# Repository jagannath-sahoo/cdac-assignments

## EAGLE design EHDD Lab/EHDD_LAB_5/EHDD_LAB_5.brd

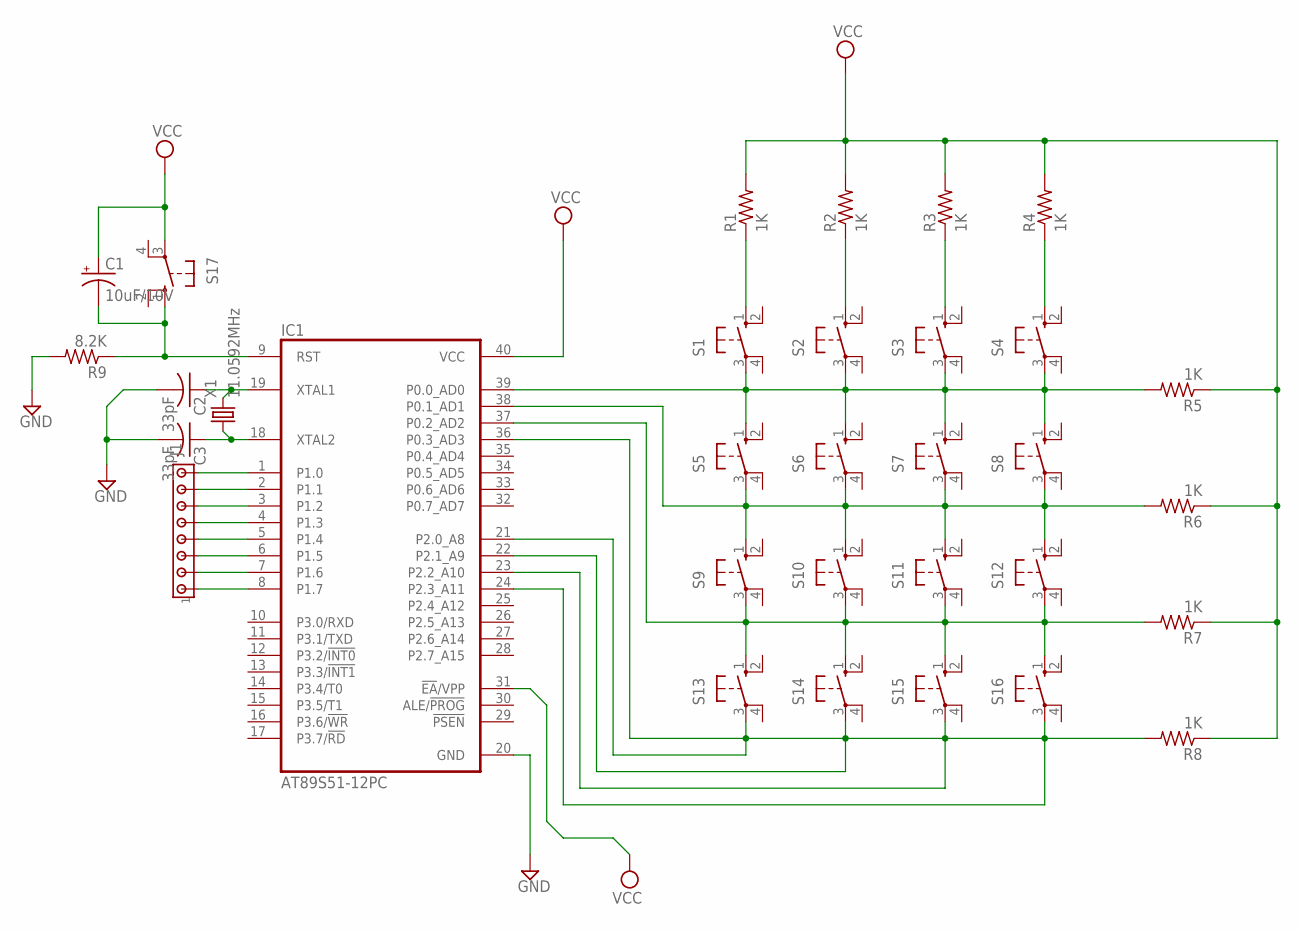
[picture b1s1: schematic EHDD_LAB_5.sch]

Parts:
C1: 10uF/10V; 153CLV-0505
C2, C3: 33pF; C0603
IC1: AT89S51-12PC; DIL40
J1: MTA08-100; 10X08MTA
R1, R2, R3, R4, R5, R6, R7, R8: 1K; R0603
R9: 8.2K; R0603
S1, S2, S3, S4, S5, S6, S7, S8, S9, S10, S11, S12, S13, S14, S15, S16, S17: 10-XX; B3F-10XX
X1: 11.0592MHz; HC49

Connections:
GND: C2.2, C3.2, IC1.20 (GND), R9.2
unnamed: R1.1, S1.1 (S)
unnamed: R2.1, S2.1 (S)
unnamed: R3.1, S3.1 (S)
unnamed: R4.1, S4.1 (S)
unnamed: IC1.39 (P0.0_AD0), R5.2, S1.3, S2.3, S3.3, S4.3, S5.1 (S), S6.1 (S), S7.1 (S), S8.1 (S)
unnamed: IC1.1 (P1.0), J1.8
unnamed: IC1.2 (P1.1), J1.7
unnamed: IC1.38 (P0.1_AD1), R6.2, S5.3, S6.3, S7.3, S8.3, S9.1 (S), S10.1 (S), S11.1 (S), S12.1 (S)
unnamed: IC1.3 (P1.2), J1.6
unnamed: IC1.4 (P1.3), J1.5
unnamed: IC1.5 (P1.4), J1.4
unnamed: IC1.37 (P0.2_AD2), R7.2, S9.3, S10.3, S11.3, S12.3, S13.1 (S), S14.1 (S), S15.1 (S), S16.1 (S)
unnamed: IC1.6 (P1.5), J1.3
unnamed: IC1.7 (P1.6), J1.2
unnamed: IC1.8 (P1.7), J1.1
unnamed: IC1.21 (P2.0_A8), IC1.22 (P2.1_A9), IC1.23 (P2.2_A10), IC1.24 (P2.3_A11), IC1.36 (P0.3_AD3), R8.2, S13.3, S14.3, S15.3, S16.3
unnamed: C1.-, IC1.9 (RST), R9.1, S17.1 (S)
unnamed: C2.1, IC1.19 (XTAL1), X1.2
unnamed: C3.1, IC1.18 (XTAL2), X1.1
VCC: C1.+, IC1.31 (!EA!/VPP), IC1.40 (VCC), R1.2, R2.2, R3.2, R4.2, R5.1, R6.1, R7.1, R8.1, S17.3

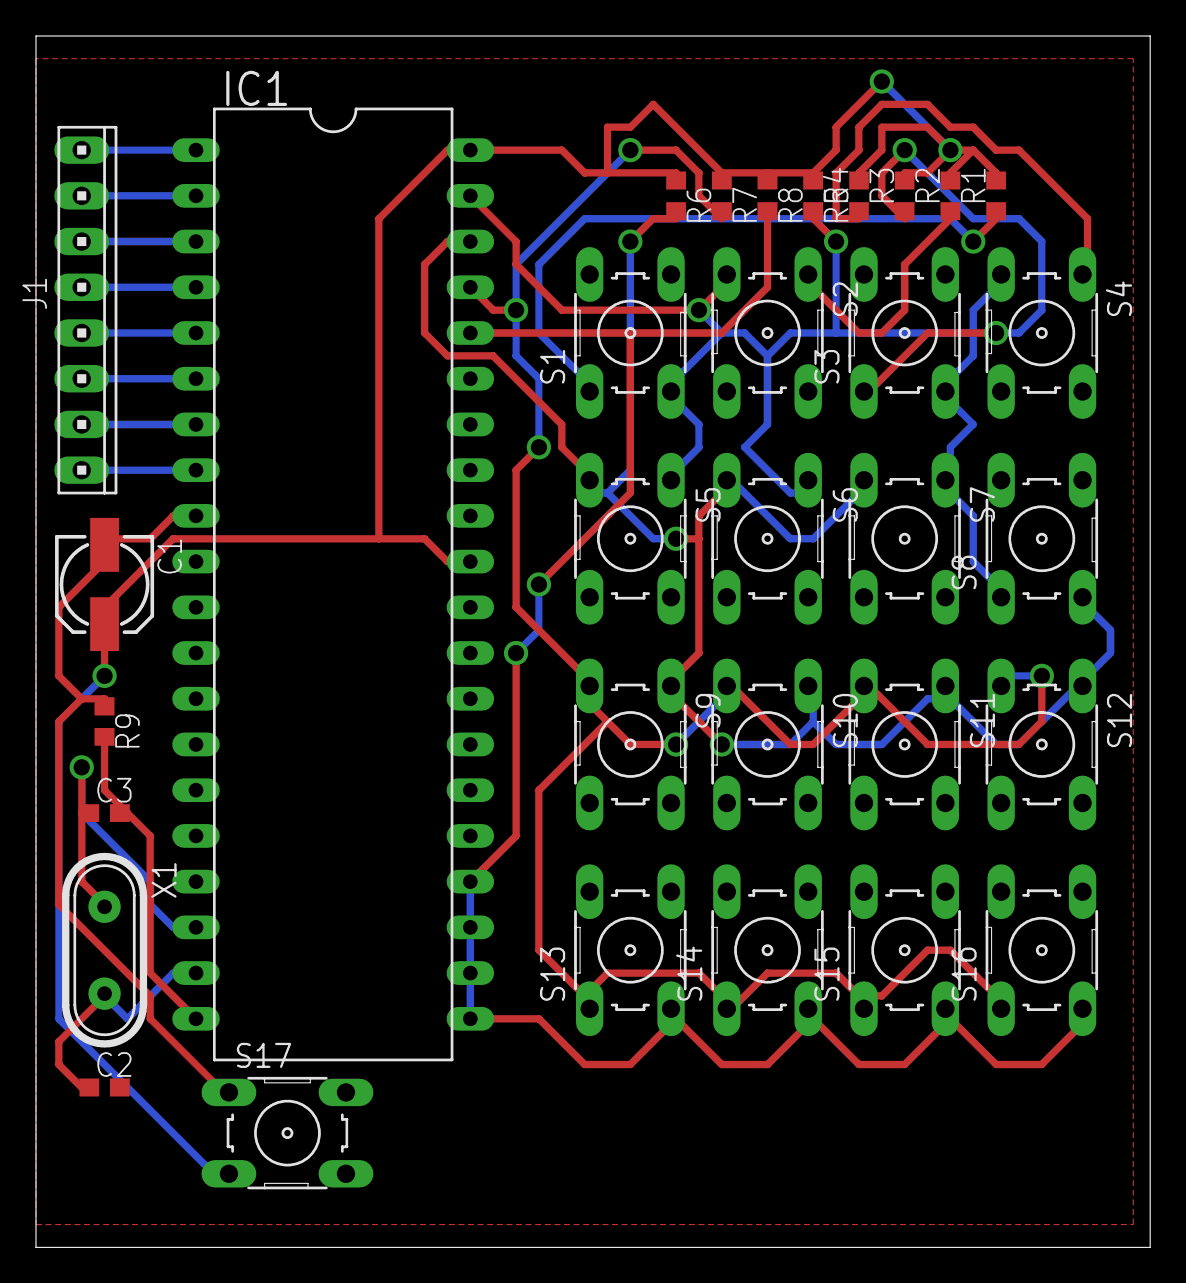
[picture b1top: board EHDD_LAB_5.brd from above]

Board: 2 copper layers, 61.9 x 67.3 mm, 32 parts (0 on the bottom side), 21 nets.

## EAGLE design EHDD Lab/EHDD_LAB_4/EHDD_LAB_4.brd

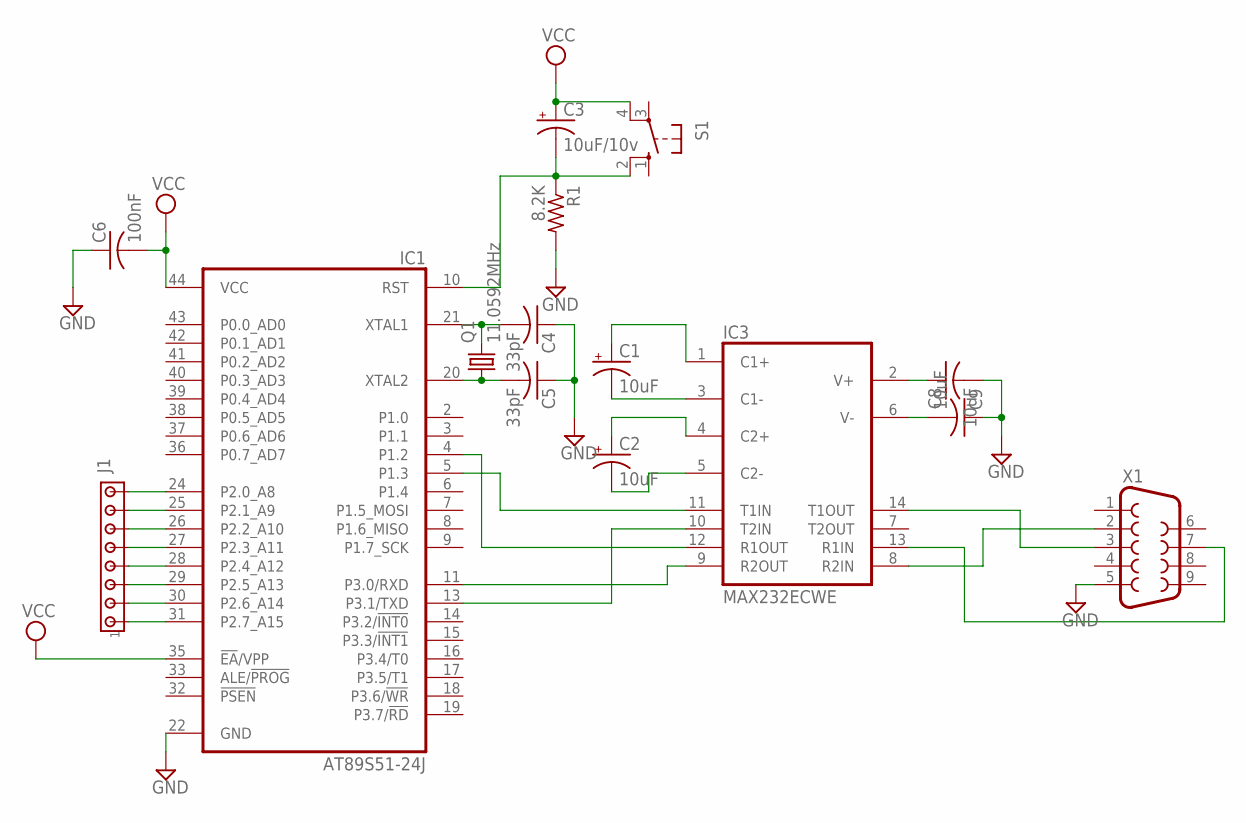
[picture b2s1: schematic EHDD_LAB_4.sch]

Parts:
C1, C2: 10uF; 153CLV-0405
C3: 10uF/10v; 153CLV-0405
C4, C5: 33pF; C0805
C6: 100nF; C0805
C8, C9: 10uF; C0805
IC1: AT89S51-24J; PLCC44
IC3: MAX232ECWE; SO16L
J1: MTA08-100; 10X08MTA
Q1: 11.0592MHz; TC38H
R1: 8.2K; R0805
S1: 10-XX; B3F-10XX
X1: F09V

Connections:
GND: C4.1, C5.1, C6.1, C8.2, C9.1, IC1.22 (GND), IC3.15 (GND), R1.2, X1.5
unnamed: IC1.5 (P1.3), IC3.11 (T1IN)
unnamed: IC1.13 (P3.1/TXD), IC3.10 (T2IN)
unnamed: IC1.4 (P1.2), IC3.12 (R1OUT)
unnamed: IC1.11 (P3.0/RXD), IC3.9 (R2OUT)
unnamed: C2.-, IC3.5 (C2-)
unnamed: C2.+, IC3.4 (C2+)
unnamed: C1.-, IC3.3 (C1-)
unnamed: C1.+, IC3.1 (C1+)
unnamed: C9.2, IC3.6 (V-)
unnamed: C8.1, IC3.2 (V+)
unnamed: IC3.14 (T1OUT), X1.3
unnamed: IC3.8 (R2IN), X1.2
unnamed: IC3.13 (R1IN), X1.7
unnamed: IC1.24 (P2.0_A8), J1.8
unnamed: IC1.25 (P2.1_A9), J1.7
unnamed: IC1.26 (P2.2_A10), J1.6
unnamed: IC1.27 (P2.3_A11), J1.5
unnamed: IC1.28 (P2.4_A12), J1.4
unnamed: IC1.29 (P2.5_A13), J1.3
unnamed: IC1.30 (P2.6_A14), J1.2
unnamed: IC1.31 (P2.7_A15), J1.1
unnamed: C5.2, IC1.20 (XTAL2), Q1.1
unnamed: C4.2, IC1.21 (XTAL1), Q1.2
unnamed: C3.-, IC1.10 (RST), R1.1, S1.2 (S1)
VCC: C3.+, C6.2, IC1.35 (!EA!/VPP), IC1.44 (VCC), IC3.16 (VCC), S1.4 (P1)

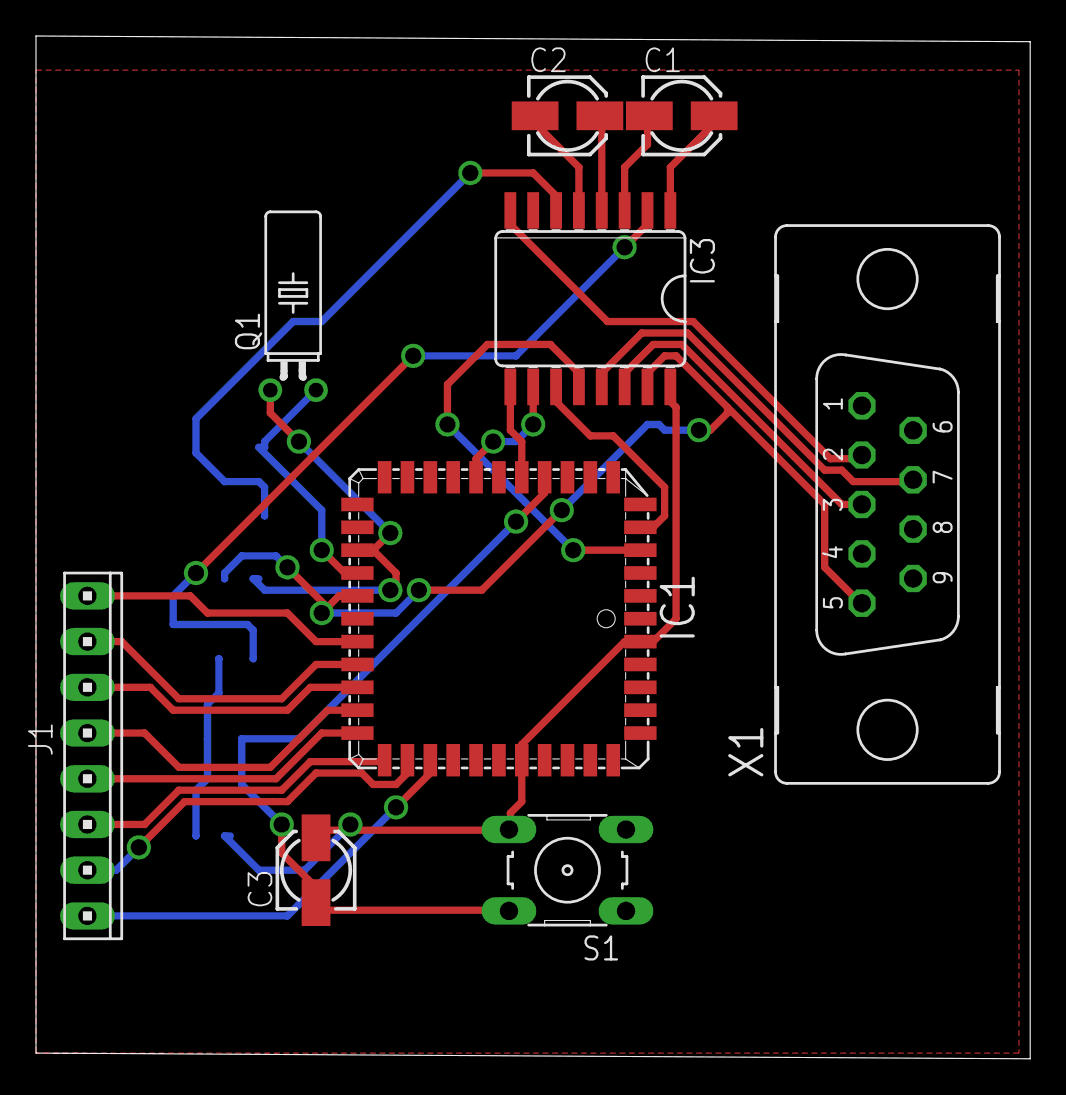
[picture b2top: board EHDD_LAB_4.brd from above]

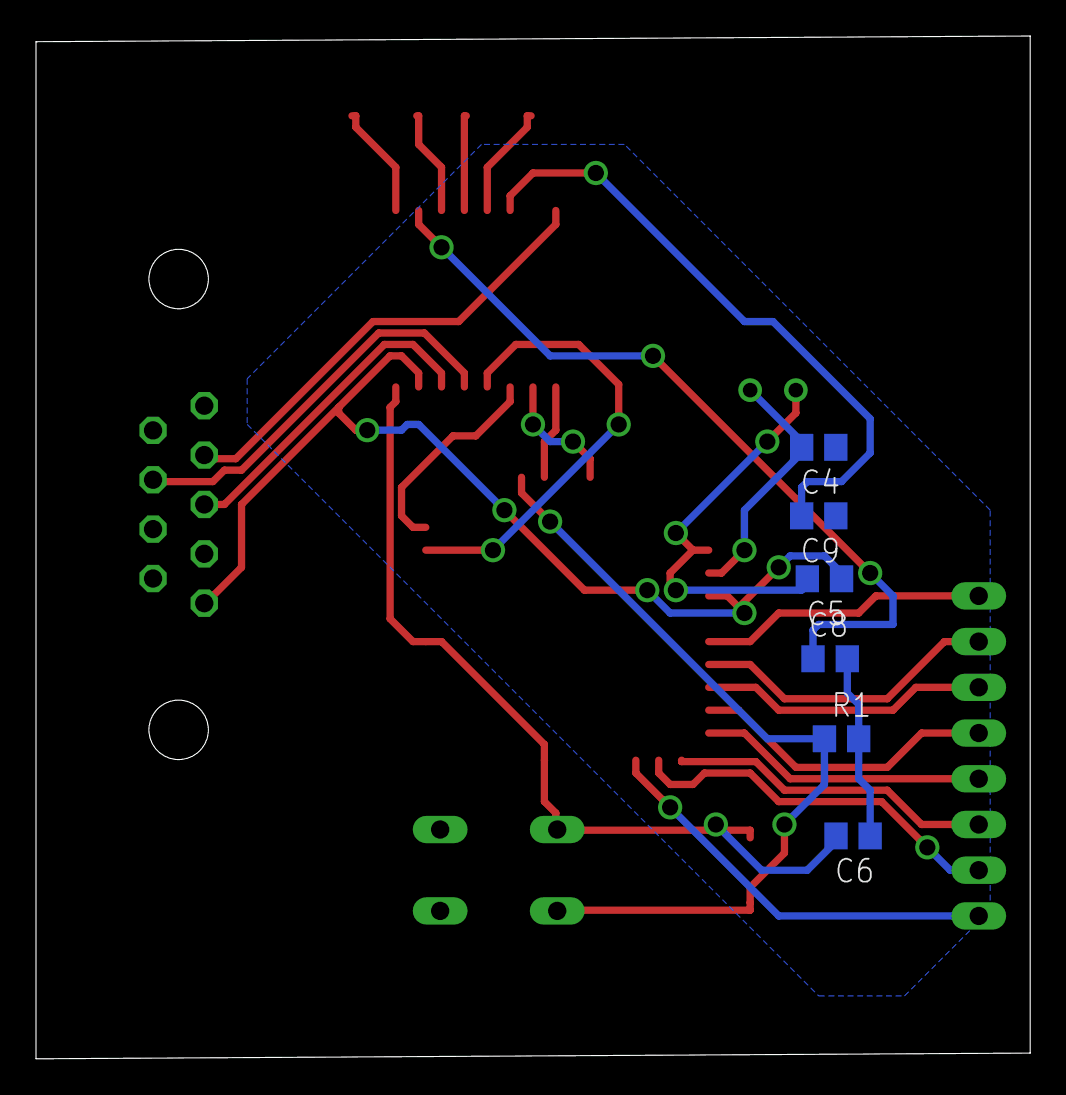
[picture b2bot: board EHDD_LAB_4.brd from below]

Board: 2 copper layers, 55.2 x 56.8 mm, 15 parts (6 on the bottom side), 26 nets.

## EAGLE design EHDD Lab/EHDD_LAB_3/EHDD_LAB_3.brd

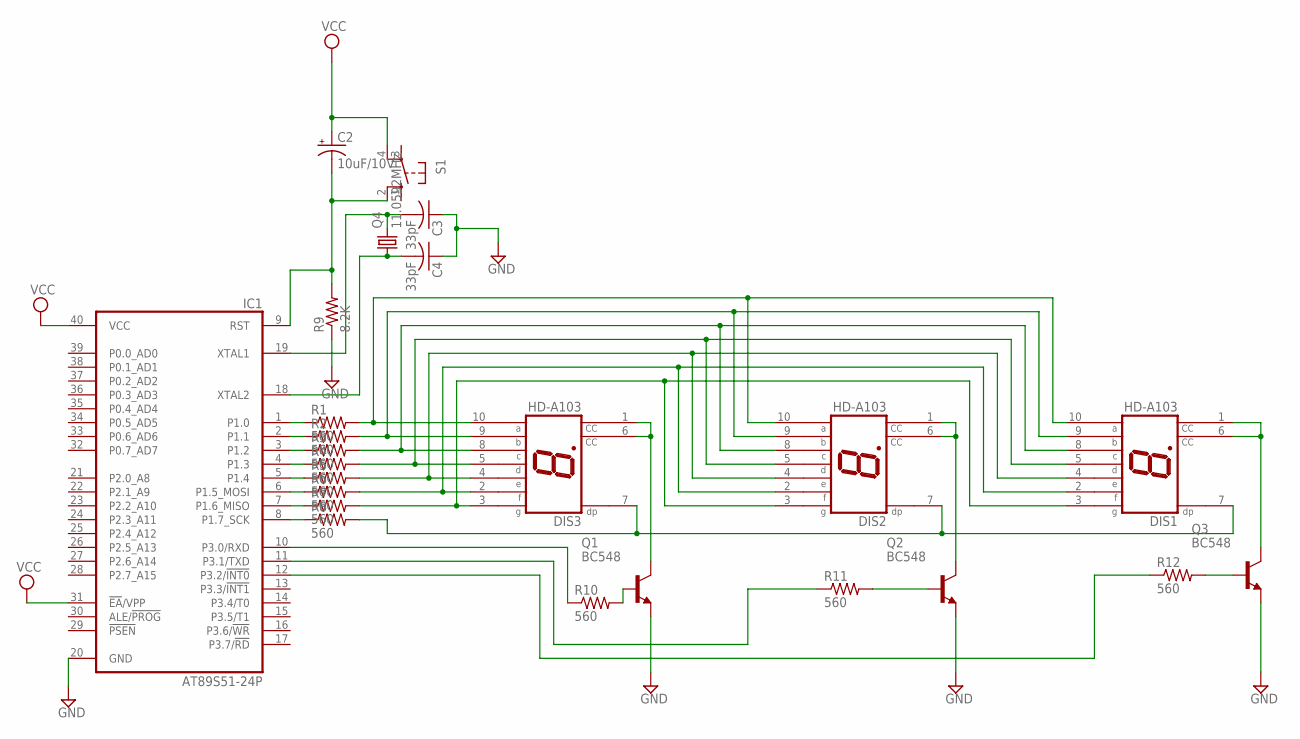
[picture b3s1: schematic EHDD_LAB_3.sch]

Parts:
C2: 10uF/10V; E2-5
C3, C4: 33pF; C025-050X050
DIS1, DIS2, DIS3: HD-A103; HDSP-A
IC1: AT89S51-24P; DIL40
Q1, Q2, Q3: BC548; TO92-EBC
Q4: 11.0592MHz; TC38H
R1, R2, R3, R4, R5, R6, R7, R8, R10, R11, R12: 560; 0207/10
R9: 8.2K; 0207/10
S1: 10-XX; B3F-10XX

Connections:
GND: C3.1, C4.1, IC1.20 (GND), Q1.E, Q2.E, Q3.E, R9.1
unnamed: DIS1.8 (C), DIS2.8 (C), DIS3.8 (C), R3.2
unnamed: DIS1.9 (B), DIS2.9 (B), DIS3.9 (B), R2.2
unnamed: DIS3.1 (CC), DIS3.6 (CC), Q1.C
unnamed: DIS1.5 (D), DIS2.5 (D), DIS3.5 (D), R4.2
unnamed: DIS1.4 (E), DIS2.4 (E), DIS3.4 (E), R5.2
unnamed: DIS1.2 (F), DIS2.2 (F), DIS3.2 (F), R6.2
unnamed: DIS1.3 (G), DIS2.3 (G), DIS3.3 (G), R7.2
unnamed: DIS1.7 (DP), DIS2.7 (DP), DIS3.7 (DP), R8.2
unnamed: IC1.1 (P1.0), R1.1
unnamed: IC1.2 (P1.1), R2.1
unnamed: IC1.3 (P1.2), R3.1
unnamed: IC1.4 (P1.3), R4.1
unnamed: IC1.5 (P1.4), R5.1
unnamed: IC1.6 (P1.5_MOSI), R6.1
unnamed: IC1.7 (P1.6_MISO), R7.1
unnamed: IC1.8 (P1.7_SCK), R8.1
unnamed: DIS1.10 (A), DIS2.10 (A), DIS3.10 (A), R1.2
unnamed: DIS2.1 (CC), DIS2.6 (CC), Q2.C
unnamed: DIS1.1 (CC), DIS1.6 (CC), Q3.C
unnamed: IC1.10 (P3.0/RXD), R10.1
unnamed: IC1.11 (P3.1/TXD), R11.1
unnamed: IC1.12 (P3.2/!INT0), R12.1
unnamed: C2.-, IC1.9 (RST), R9.2, S1.2 (S1)
unnamed: Q1.B, R10.2
unnamed: C3.2, IC1.19 (XTAL1), Q4.2
unnamed: C4.2, IC1.18 (XTAL2), Q4.1
unnamed: Q2.B, R11.2
unnamed: Q3.B, R12.2
VCC: C2.+, IC1.31 (!EA!/VPP), IC1.40 (VCC), S1.4 (P1)

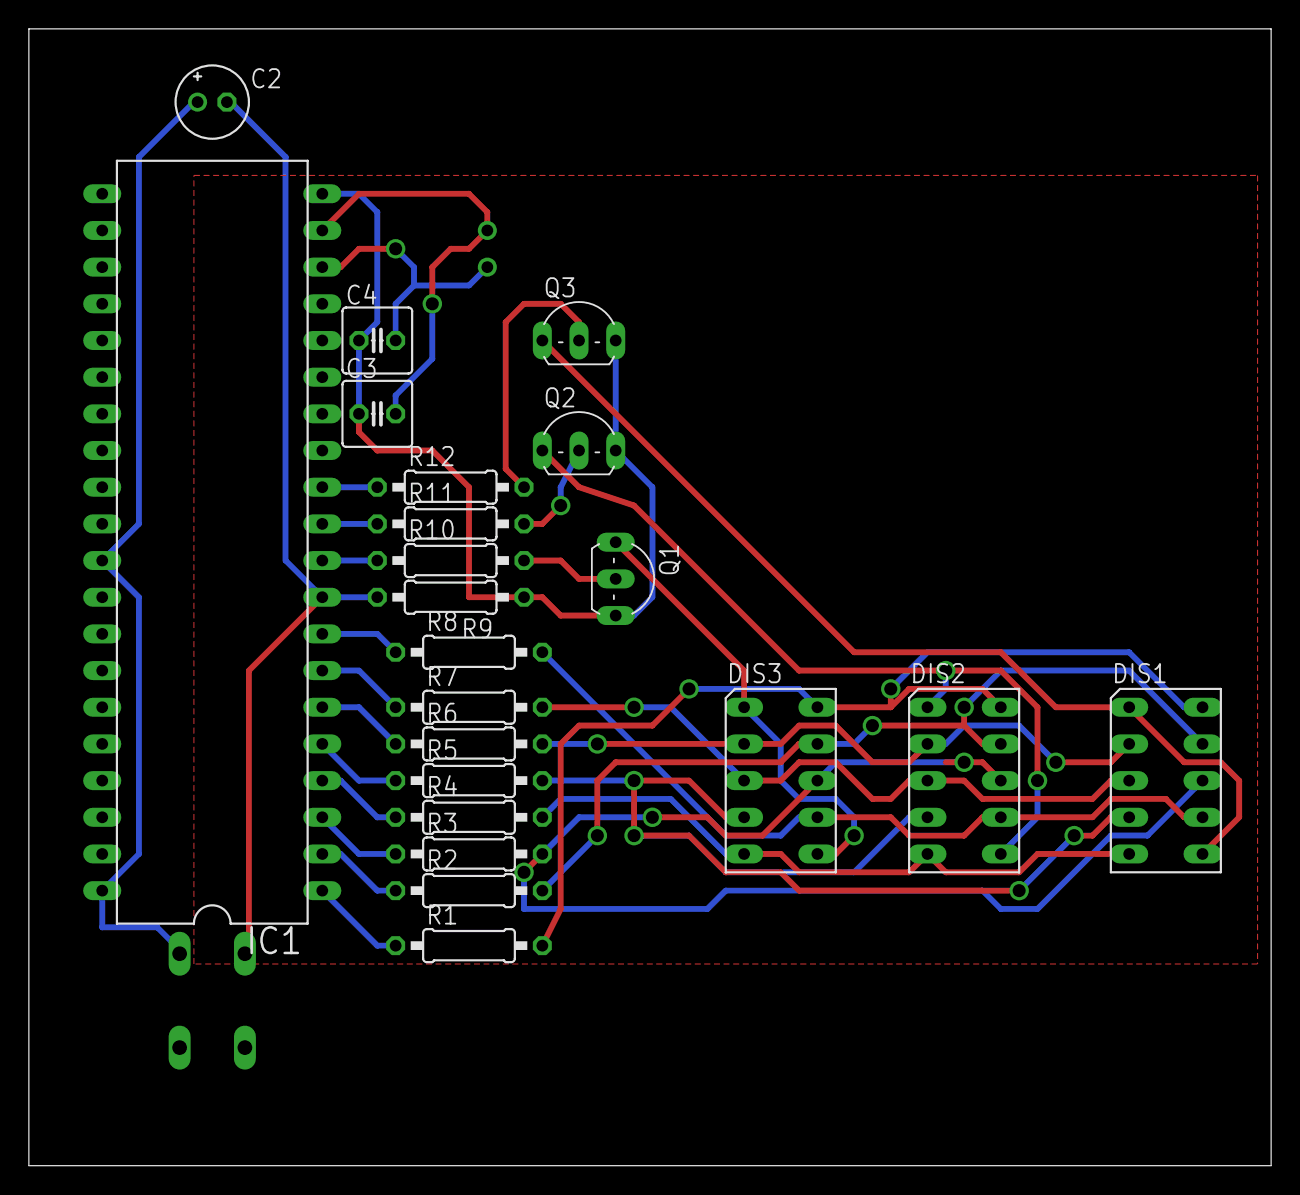
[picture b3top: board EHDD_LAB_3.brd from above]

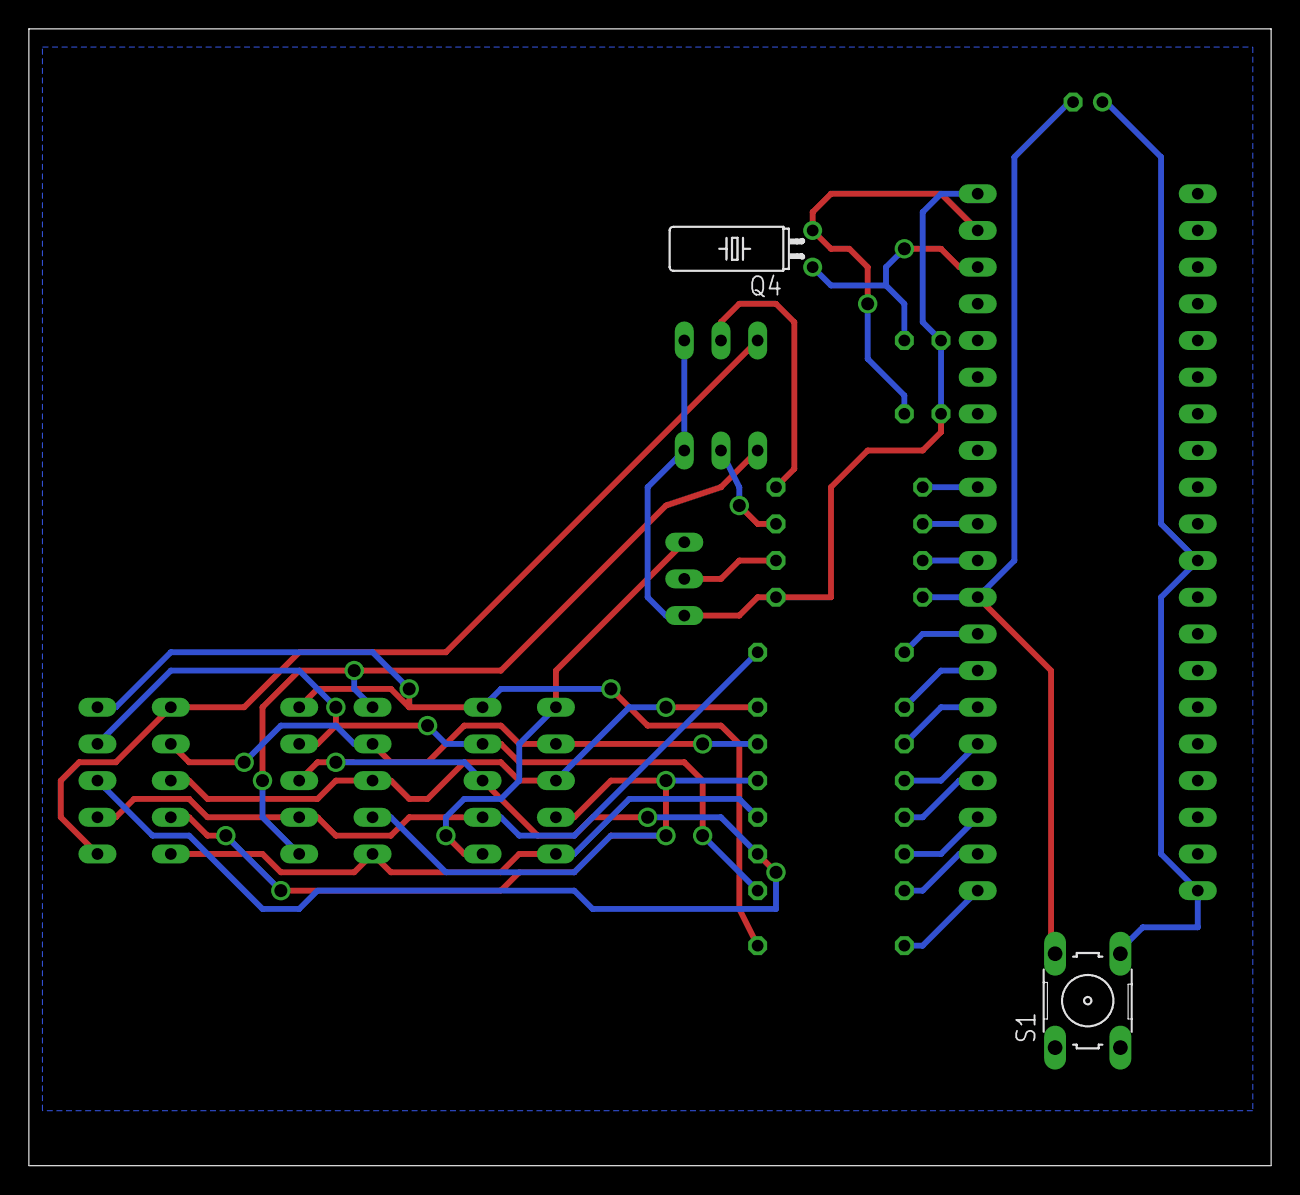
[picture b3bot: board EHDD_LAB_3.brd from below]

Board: 2 copper layers, 86.0 x 78.7 mm, 24 parts (2 on the bottom side), 30 nets.

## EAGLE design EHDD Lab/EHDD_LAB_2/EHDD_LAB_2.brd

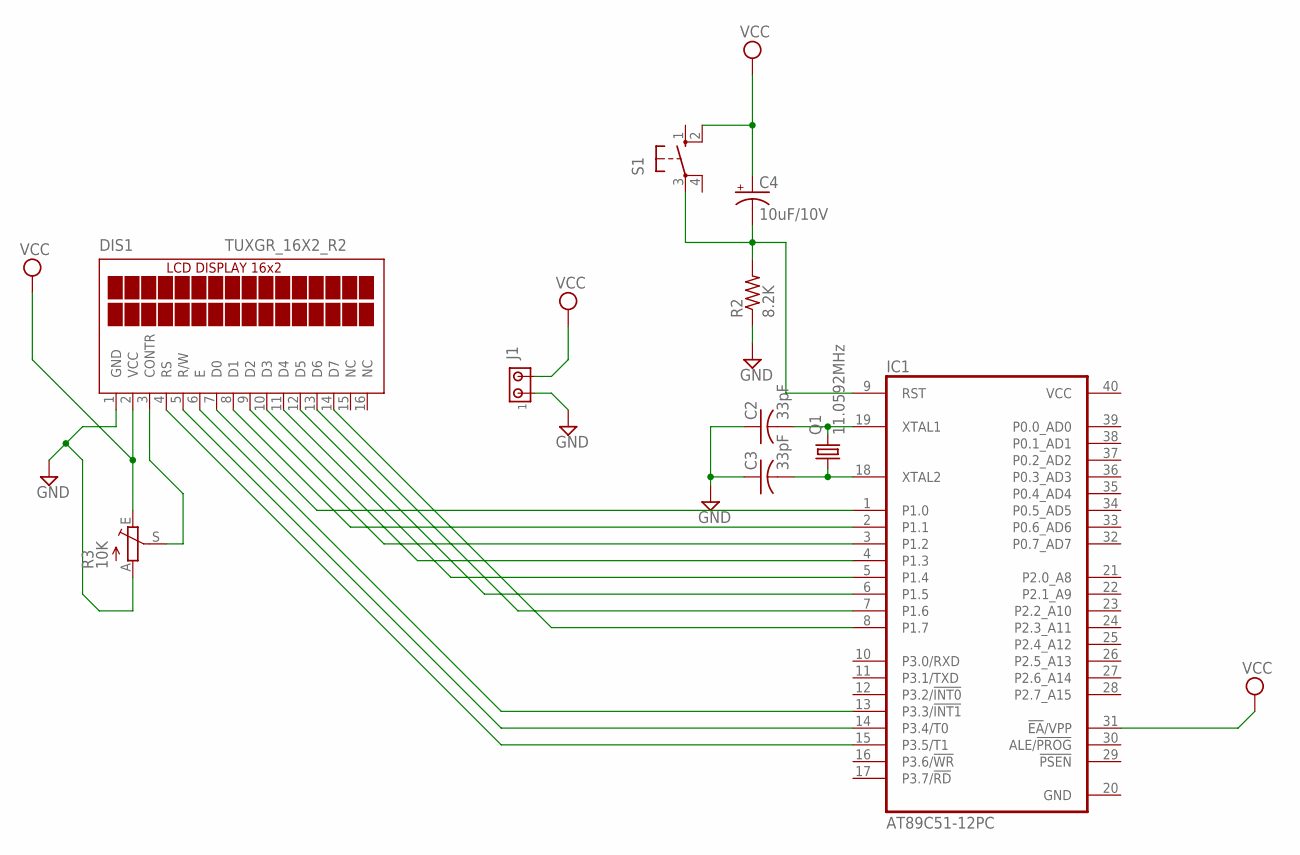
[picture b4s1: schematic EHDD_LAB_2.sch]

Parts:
C2, C3: 33pF; C025-025X050
C4: 10uF/10V; E2,5-5
DIS1: TUXGR_16X2_R2
IC1: AT89C51-12PC; DIL40
J1: MTA02-100; 10X02MTA
Q1: 11.0592MHz; TC26H
R2: 8.2K; R2512
R3: 10K; B25U
S1: 10-XX; B3F-10XX

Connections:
GND: C2.1, C3.1, DIS1.1 (GND), IC1.20 (GND), J1.1, R2.1, R3.A
unnamed: C4.-, IC1.9 (RST), R2.2, S1.3
unnamed: C2.2, IC1.19 (XTAL1), Q1.2
unnamed: C3.2, IC1.18 (XTAL2), Q1.1
unnamed: DIS1.7 (D0), IC1.1 (P1.0)
unnamed: DIS1.8 (D1), IC1.2 (P1.1)
unnamed: DIS1.9 (D2), IC1.3 (P1.2)
unnamed: DIS1.10 (D3), IC1.4 (P1.3)
unnamed: DIS1.11 (D4), IC1.5 (P1.4)
unnamed: DIS1.12 (D5), IC1.6 (P1.5)
unnamed: DIS1.13 (D6), IC1.7 (P1.6)
unnamed: DIS1.14 (D7), IC1.8 (P1.7)
unnamed: DIS1.6 (E), IC1.13 (P3.3/!INT1)
unnamed: DIS1.5 (R/W), IC1.14 (P3.4/T0)
unnamed: DIS1.4 (RS), IC1.15 (P3.5/T1)
unnamed: DIS1.3 (CONTR), R3.S
VCC: C4.+, DIS1.2 (VCC), IC1.31 (!EA!/VPP), IC1.40 (VCC), J1.2, R3.E, S1.2 (S1)

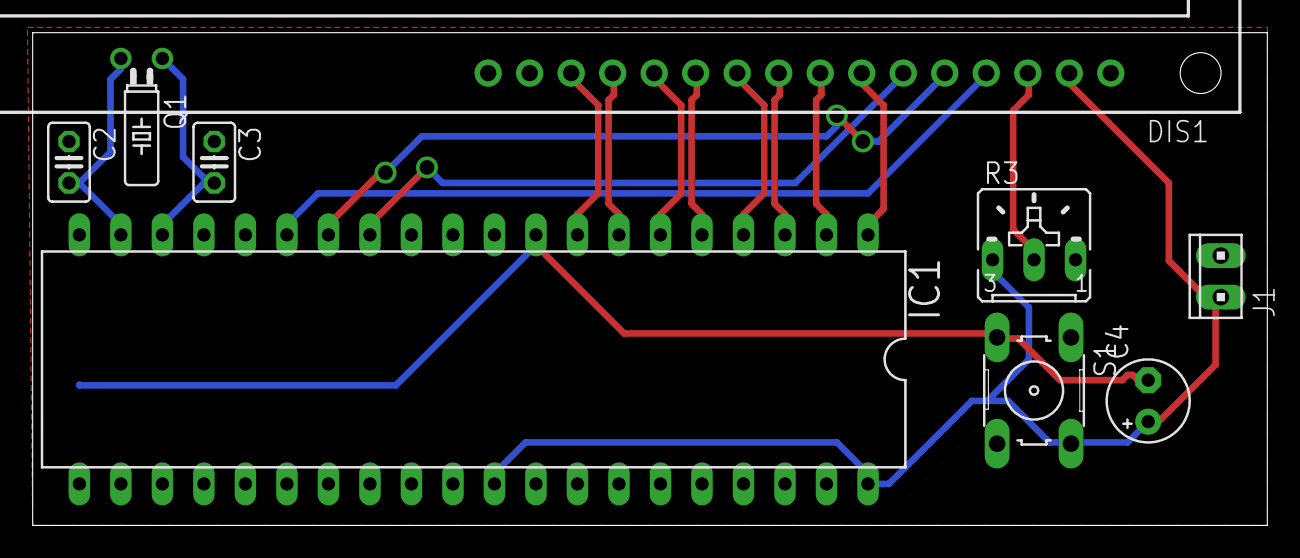
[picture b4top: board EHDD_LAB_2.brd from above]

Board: 2 copper layers, 75.6 x 30.2 mm, 10 parts (1 on the bottom side), 17 nets.

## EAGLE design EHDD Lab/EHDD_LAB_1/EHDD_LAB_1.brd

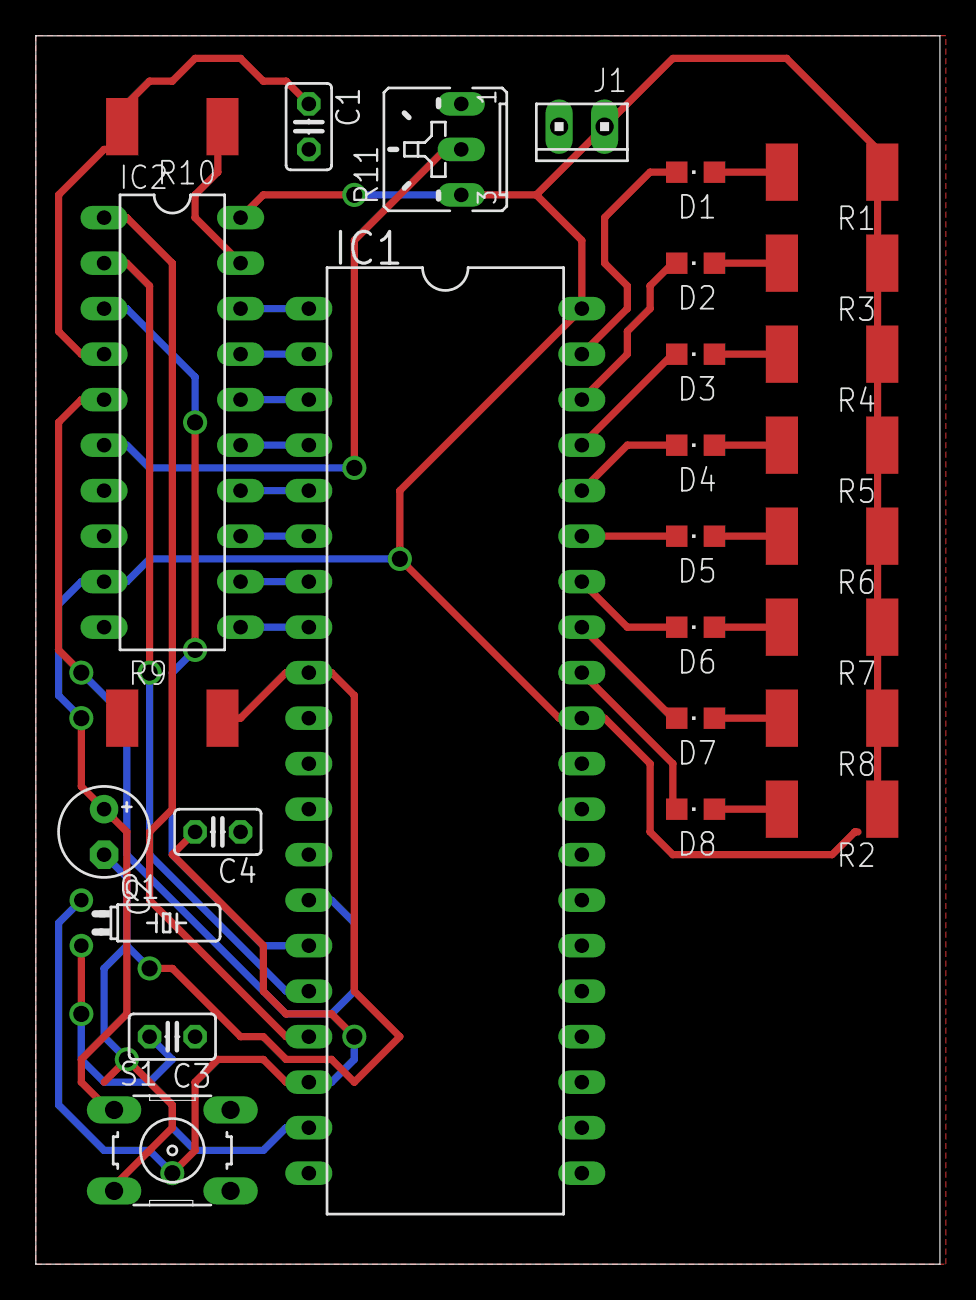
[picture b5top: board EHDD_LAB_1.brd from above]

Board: 2 copper layers, 50.5 x 68.6 mm, 28 parts (0 on the bottom side), 36 nets.

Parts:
C1: 150uF; C025-025X050
C2: 10uF/10V; E2,5-5
C3, C4: 33pF; C025-025X050
D1, D2, D3, D4, D5, D6, D7, D8: CHIPLED_0805
IC1: AT89C51-12PC; DIL40
IC2: ADC0801; DIL20
J1: 10X02MTA
Q1: 11.0592MHz; TC26H
R1, R2, R3, R4, R5, R6, R7, R8: R2512
R9: 8.2K; R2512
R10: 10K; R2512
R11: 10K; B25U
S1: Reset; B3F-10XX

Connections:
CS: IC1.17, IC2.1
GND: C1.2, C3.1, C4.1, IC1.20, IC2.7, IC2.8, IC2.10, J1.1, R9.1, R11.A
INTR: IC1.14, IC2.5
unnamed: IC1.1, IC2.18
unnamed: IC1.2, IC2.17
unnamed: IC1.3, IC2.16
unnamed: IC1.4, IC2.15
unnamed: IC1.5, IC2.14
unnamed: IC1.6, IC2.13
unnamed: IC1.7, IC2.12
unnamed: IC1.8, IC2.11
unnamed: C2.-, IC1.9, R9.2, S1.3
unnamed: C3.2, IC1.19, Q1.2
unnamed: D1.C, IC1.39
unnamed: D2.C, IC1.38
unnamed: D3.C, IC1.37
unnamed: C4.2, IC1.18, Q1.1
unnamed: D4.C, IC1.36
unnamed: D5.C, IC1.35
unnamed: D6.C, IC1.34
unnamed: D7.C, IC1.33
unnamed: D8.C, IC1.32
unnamed: D1.A, R1.2
unnamed: D2.A, R3.2
unnamed: D3.A, R4.2
unnamed: D4.A, R5.2
unnamed: D5.A, R6.2
unnamed: D6.A, R7.2
unnamed: D7.A, R8.2
unnamed: D8.A, R2.2
unnamed: IC2.6, R11.S
unnamed: IC2.19, R10.1
unnamed: C1.1, IC2.4, R10.2
RD: IC1.16, IC2.2
VCC: C2.+, IC1.31, IC1.40, IC2.9, IC2.20, J1.2, R1.1, R2.1, R3.1, R4.1, R5.1, R6.1, R7.1, R8.1, R11.E, S1.1
WR: IC1.15, IC2.3

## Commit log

2019-02-23 demo.txt new
2019-02-25 assignment_3
2019-02-26 assignment_5
2019-02-27 auto.sh
2019-02-27 Assignment_3 q1.c
2019-02-27 Assignment_5 Done
2019-02-27 auto.sh modified
2019-02-27 a2,b2,c2
2019-02-28 Assignment 6 update
2019-02-28 assignment_6 q12
2019-03-01 assignment12 done
2019-03-04 Assignment_7 Added
2019-03-05 assignment 8 started
2019-03-07 Assignment_DS
2019-03-07 Assignment_9 done
2019-03-08 DS update
2019-03-09 Assign_9 update
2019-03-12 Java NEW
2019-03-13 Java file
2019-03-13 Practice C Prog
2019-03-13 Practice
2019-03-15 Practice Sorting
2019-03-15 Practice LinkedList
2019-03-16 AVR Lab's LCD
2019-03-16 Music AVR
2019-03-17 OS DAY1
2019-03-22 UART to LCD
2019-03-22 LCD TO UART Update
2019-03-24 AVR CALCULATOR
2019-03-24 CACULATOR DONE
2019-03-24 LCD,STOPWATCH
2019-03-25 Java Codes
2019-03-26 C&DS Assin Zip
2019-04-02 EHDD Lab Update
2019-04-02 File Handling
2019-04-03 EHDD LAB3
2019-04-04 EHDD Labs
2019-04-18 Socket Programming
2019-04-24 Java Update-Workspace-update
2022-12-08 Bump qs, body-parser and express
    Bumps [qs](https://github.com/ljharb/qs) to 6.5.3 and updates ancestor dependencies [qs](https://github.com/ljharb/qs), [body-parser](https://github.com/expressjs/body-parser) and [express](https://g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
    Updates `qs` from 6.5.2 to 6.5.3
    - [Release notes](https://github.com/ljharb/qs/releases)
    - [Changelog](https://github.com/ljharb/qs/blob/main/CHANGELOG.md)
    - [Commits](https://github.com/ljharb/qs/compare/v6.5.2...v6.5.3)
    Updates `body-parser` from 1.18.3 to 1.20.1
2022-12-09 Bump express in /python/REST/REST-Practice/nodejs-restapi
    Bumps [express](https://github.com/expressjs/express) from 4.16.4 to 4.17.3.
    - [Release notes](https://github.com/expressjs/express/releases)
    - [Changelog](https://github.com/expressjs/express/blob/master/History.md)
    - [Commits](https://github.com/expressjs/express/compare/4.16.4...4.17.3)
    ---
    updated-dependencies:
